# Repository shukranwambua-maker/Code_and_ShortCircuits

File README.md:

# Code&ShortCircuits
"Those who don't INNOVATE perish!!!!!" - Muchai Wambua

Ever wondered what an ESP32-WROOM-32D Development board entails???

Schematic:

Footprint:

3D Image:

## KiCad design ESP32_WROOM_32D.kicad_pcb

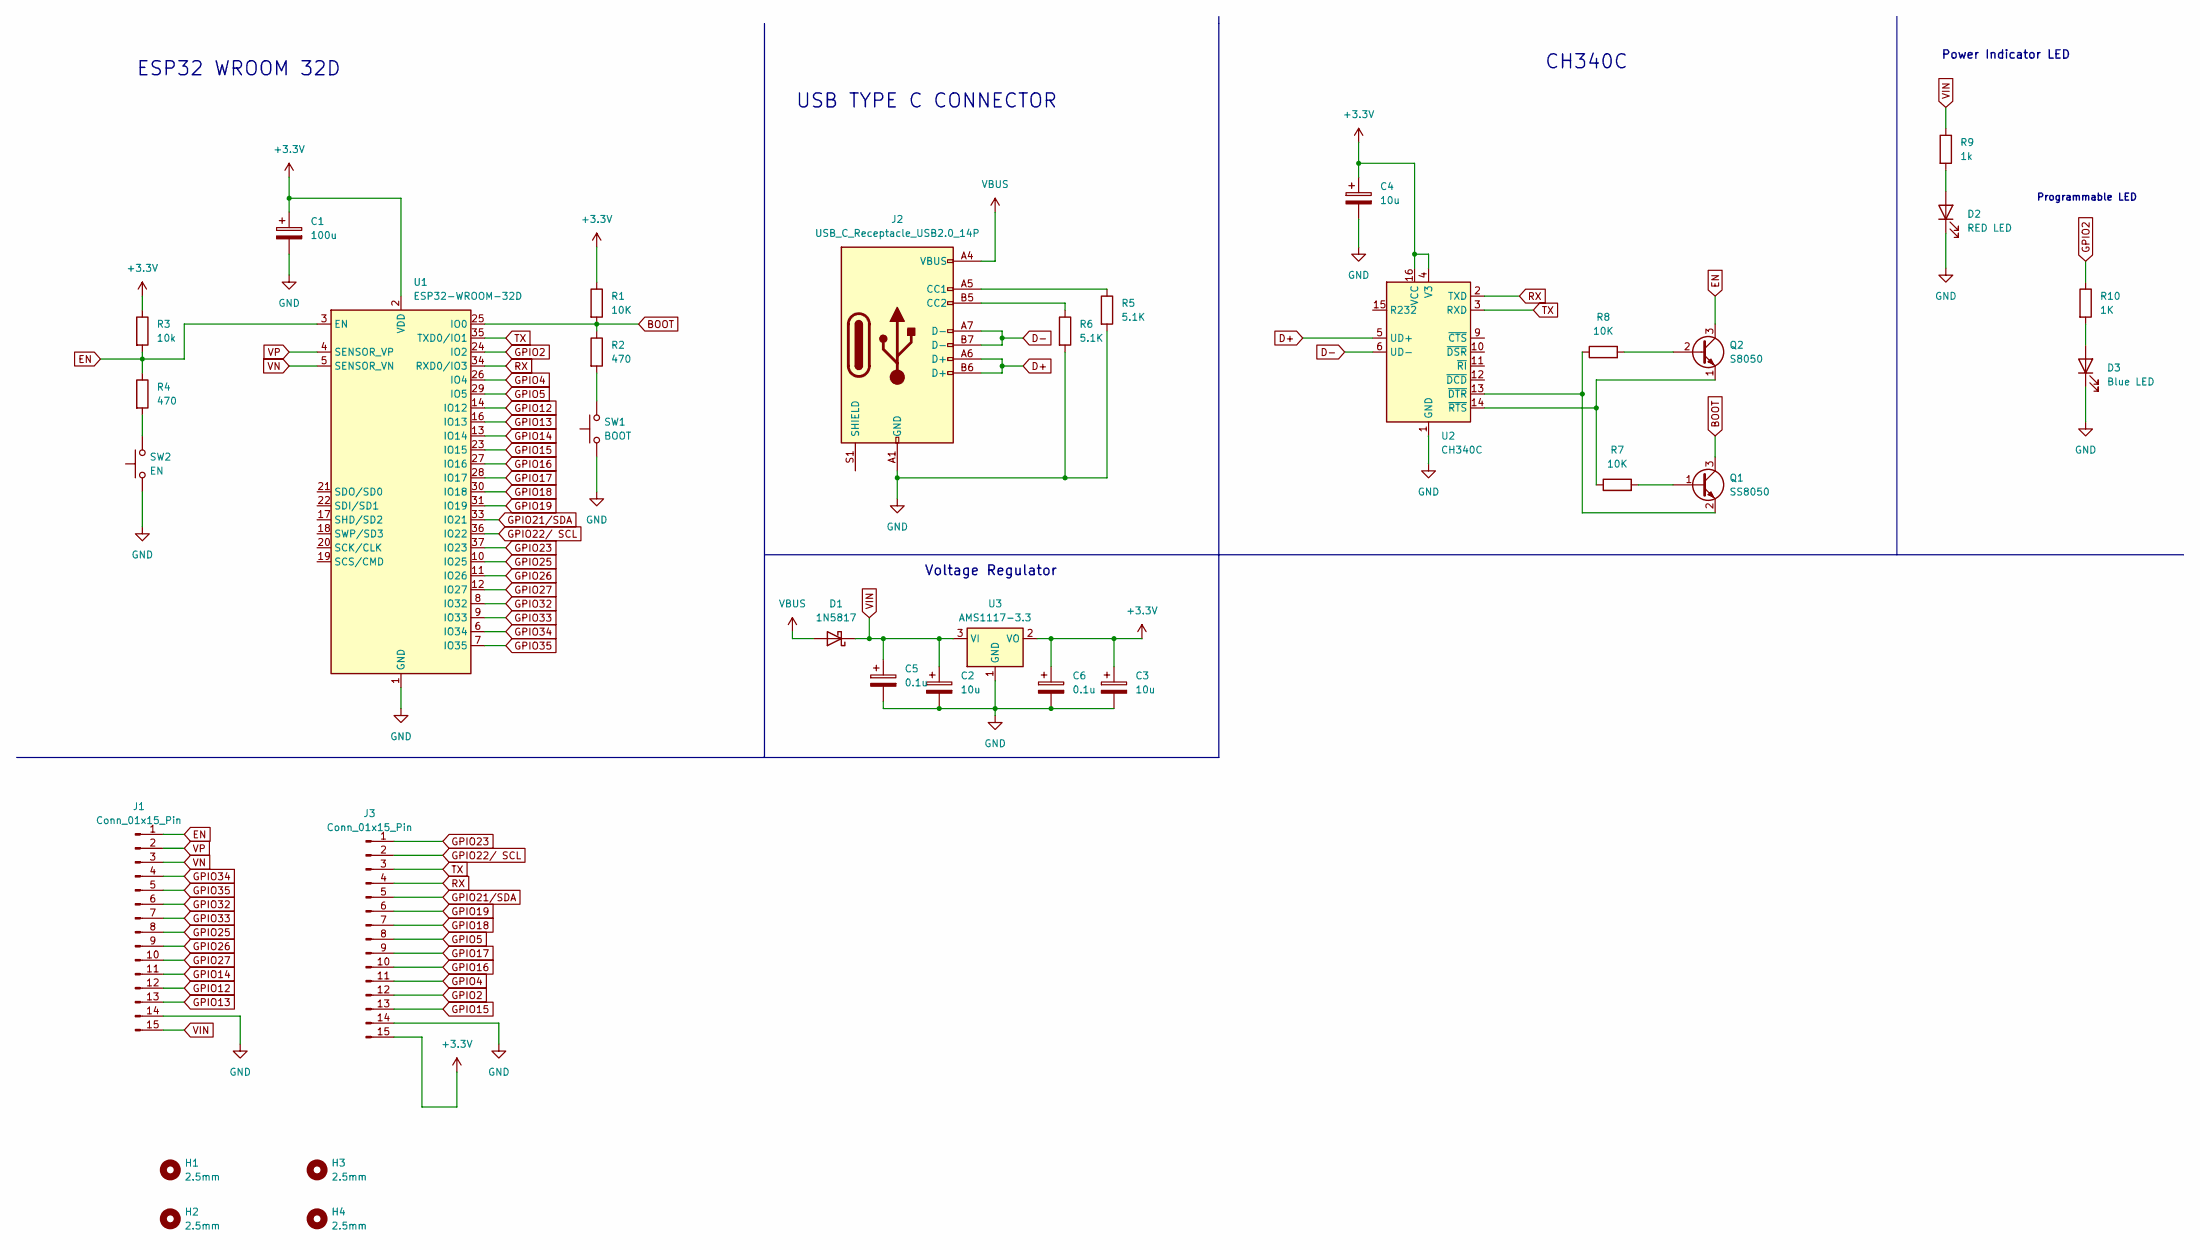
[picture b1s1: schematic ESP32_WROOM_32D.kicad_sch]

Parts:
C1: 100u; C_0805_2012Metric_Pad1.18x1.45mm_HandSolder
C2, C3, C4: 10u; C_0805_2012Metric_Pad1.18x1.45mm_HandSolder
C5, C6: 0.1u; C_0805_2012Metric_Pad1.18x1.45mm_HandSolder
D1: 1N5817; D_SOD-123
D2: RED LED; LED_0805_2012Metric_Pad1.15x1.40mm_HandSolder
D3: Blue LED; LED_0805_2012Metric_Pad1.15x1.40mm_HandSolder
H1, H2, H3, H4: 2.5mm; MountingHole_2.5mm
J1, J3: Conn_01x15_Pin; PinHeader_1x15_P1.00mm_Vertical
J2: USB_C_Receptacle_USB2.0_14P; USB_C_Receptacle_G-Switch_GT-USB-7010ASV
Q1: SS8050; SOT-23
Q2: S8050; SOT-23
R1, R7, R8: 10K; R_0805_2012Metric_Pad1.20x1.40mm_HandSolder
R2, R4: 470; R_0805_2012Metric_Pad1.20x1.40mm_HandSolder
R3: 10k; R_0805_2012Metric_Pad1.20x1.40mm_HandSolder
R5, R6: 5.1K; R_0805_2012Metric_Pad1.20x1.40mm_HandSolder
R9: 1k; R_0805_2012Metric_Pad1.20x1.40mm_HandSolder
R10: 1K; R_0805_2012Metric_Pad1.20x1.40mm_HandSolder
SW1: BOOT; SW_Tactile_SPST_NO_Straight_CK_PTS636Sx25SMTRLFS
SW2: EN; SW_Tactile_SPST_NO_Straight_CK_PTS636Sx25SMTRLFS
U1: ESP32-WROOM-32D
U2: CH340C; SOIC-16_3.9x9.9mm_P1.27mm
U3: AMS1117-3.3; SOT-223-3_TabPin2

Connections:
+3.3V: C1.1, C3.1, C4.1, C6.1, J3.15, R1.1, R3.1, U1.2 (VDD), U2.4 (V3), U2.16 (VCC), U3.2 (VO)
BOOT: Q1.3 (C), R1.2, R2.1, U1.25 (IO0)
D+: J2.A6 (D+), J2.B6 (D+), U2.5 (UD+)
D-: J2.A7 (D-), J2.B7 (D-), U2.6 (UD-)
EN: J1.1, Q2.3 (C), R3.2, R4.1, U1.3 (EN)
GND: C1.2, C2.2, C3.2, C4.2, C5.2, C6.2, D2.1 (K), D3.1 (K), J1.14, J2.A1 (GND), J2.A12 (GND), J2.B1 (GND), J2.B12 (GND), J3.14, R5.2, R6.2, SW1.1, SW2.1, U1.1 (GND), U1.15 (GND), U1.38 (GND), U1.39 (GND), U2.1 (GND), U3.1 (GND)
GPIO2: J3.12, R10.1, U1.24 (IO2)
GPIO4: J3.11, U1.26 (IO4)
GPIO5: J3.8, U1.29 (IO5)
GPIO12: J1.12, U1.14 (IO12)
GPIO13: J1.13, U1.16 (IO13)
GPIO14: J1.11, U1.13 (IO14)
GPIO15: J3.13, U1.23 (IO15)
GPIO16: J3.10, U1.27 (IO16)
GPIO17: J3.9, U1.28 (IO17)
GPIO18: J3.7, U1.30 (IO18)
GPIO19: J3.6, U1.31 (IO19)
GPIO21/SDA: J3.5, U1.33 (IO21)
GPIO22/ SCL: J3.2, U1.36 (IO22)
GPIO23: J3.1, U1.37 (IO23)
GPIO25: J1.8, U1.10 (IO25)
GPIO26: J1.9, U1.11 (IO26)
GPIO27: J1.10, U1.12 (IO27)
GPIO32: J1.6, U1.8 (IO32)
GPIO33: J1.7, U1.9 (IO33)
GPIO34: J1.4, U1.6 (IO34)
GPIO35: J1.5, U1.7 (IO35)
unnamed: D2.2 (A), R9.2
unnamed: D3.2 (A), R10.2
unnamed: J2.A5 (CC1), R5.1
unnamed: J2.B5 (CC2), R6.1
unnamed: Q1.1 (B), R7.2
unnamed: Q1.2 (E), R8.1, U2.13 (~DTR)
unnamed: Q2.2 (B), R8.2
unnamed: Q2.1 (E), R7.1, U2.14 (~RTS)
unnamed: R2.2, SW1.2
unnamed: R4.2, SW2.2
RX: J3.4, U1.34 (RXD0/IO3), U2.2 (TXD)
TX: J3.3, U1.35 (TXD0/IO1), U2.3 (RXD)
VBUS: D1.2 (A), J2.A4 (VBUS), J2.A9 (VBUS), J2.B4 (VBUS), J2.B9 (VBUS)
VIN: C2.1, C5.1, D1.1 (K), J1.15, R9.1, U3.3 (VI)
VN: J1.3, U1.5 (SENSOR_VN)
VP: J1.2, U1.4 (SENSOR_VP)

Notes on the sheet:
Power Indicator LED
Voltage Regulator
ESP32 WROOM 32D
USB TYPE C CONNECTOR
CH340C
Programmable LED

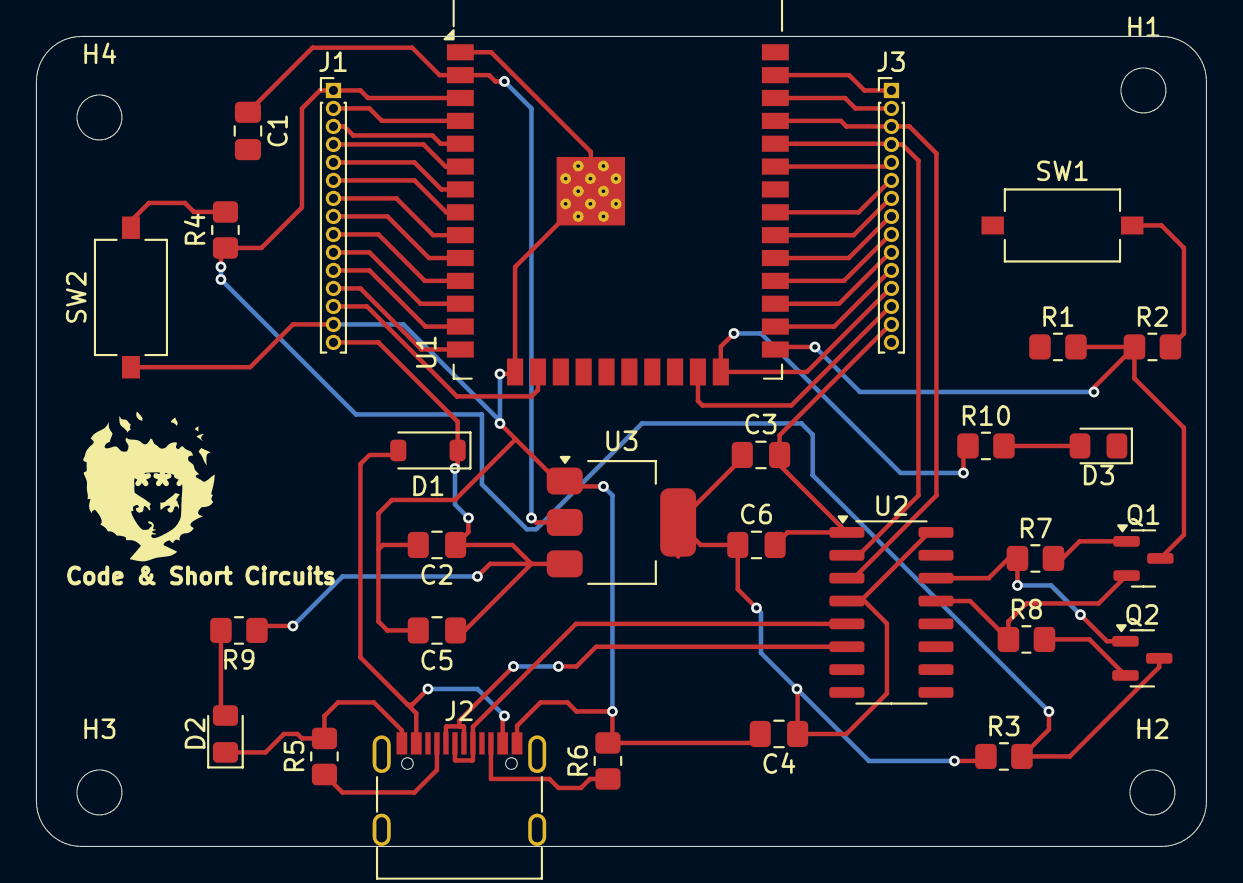
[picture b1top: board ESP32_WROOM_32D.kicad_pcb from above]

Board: 2 copper layers, 65.0 x 45.0 mm, 33 parts (0 on the bottom side), 43 nets.
